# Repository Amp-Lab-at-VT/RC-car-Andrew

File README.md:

## Members
Andrew Baltus electrical engineering 2028

## Mentor
Eddie Pritchard, Ethan James

## Current Status
IN PROGRESS

## Project Overview

h

## Educational Value Added

h
## Tasks

h

## Design Decisions

## BOM + Component Cost

## Timeline

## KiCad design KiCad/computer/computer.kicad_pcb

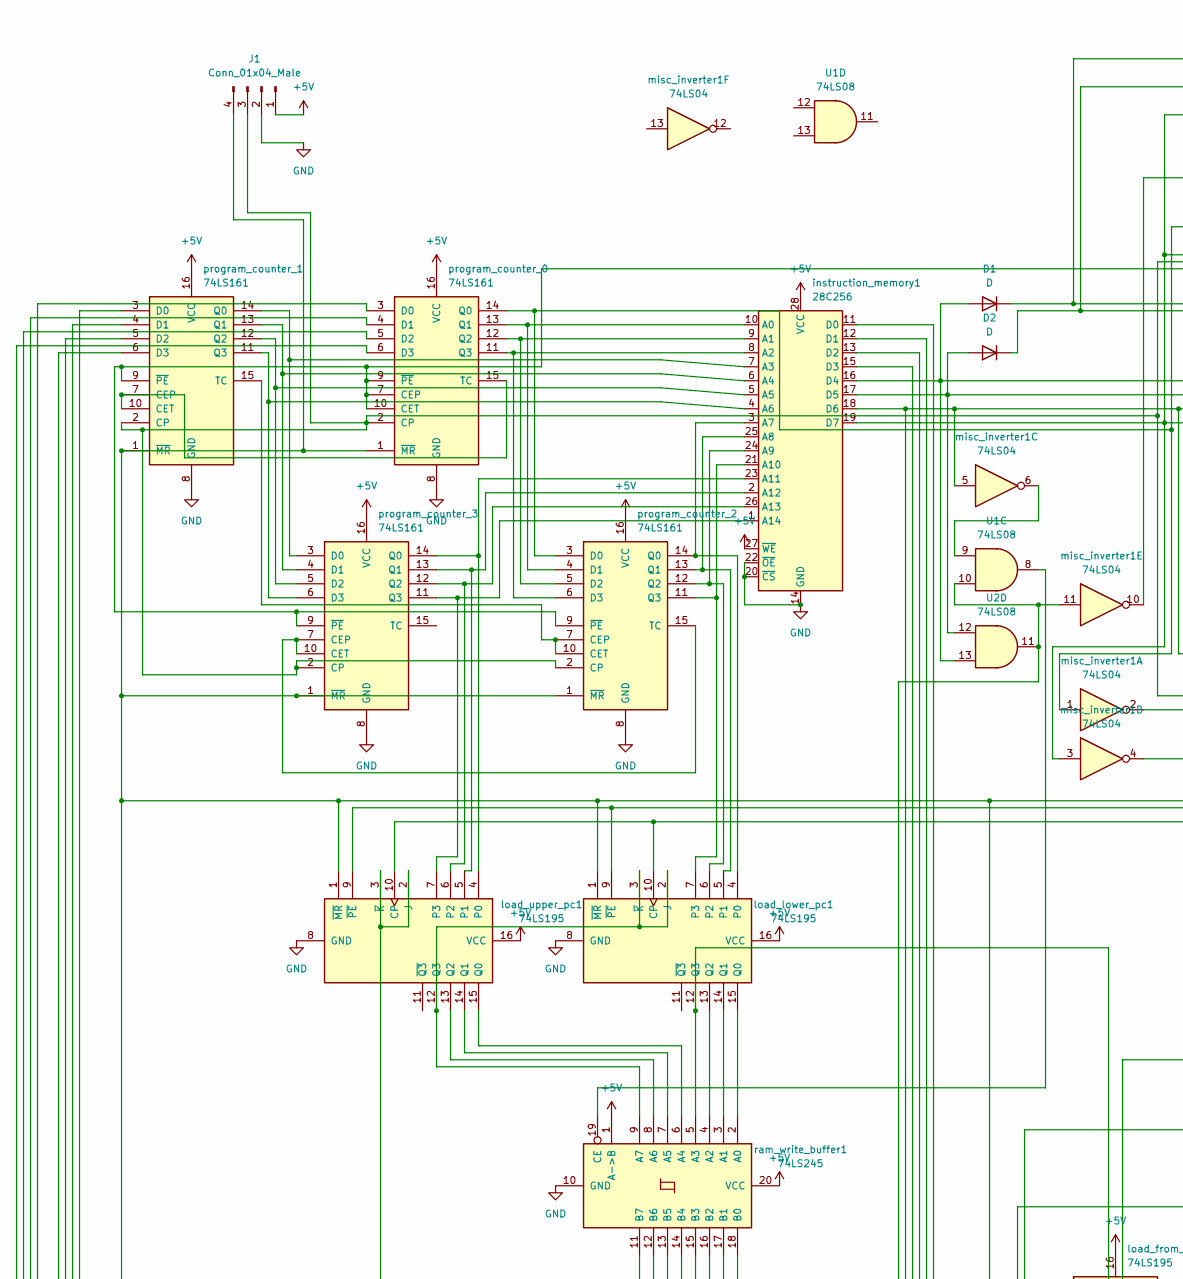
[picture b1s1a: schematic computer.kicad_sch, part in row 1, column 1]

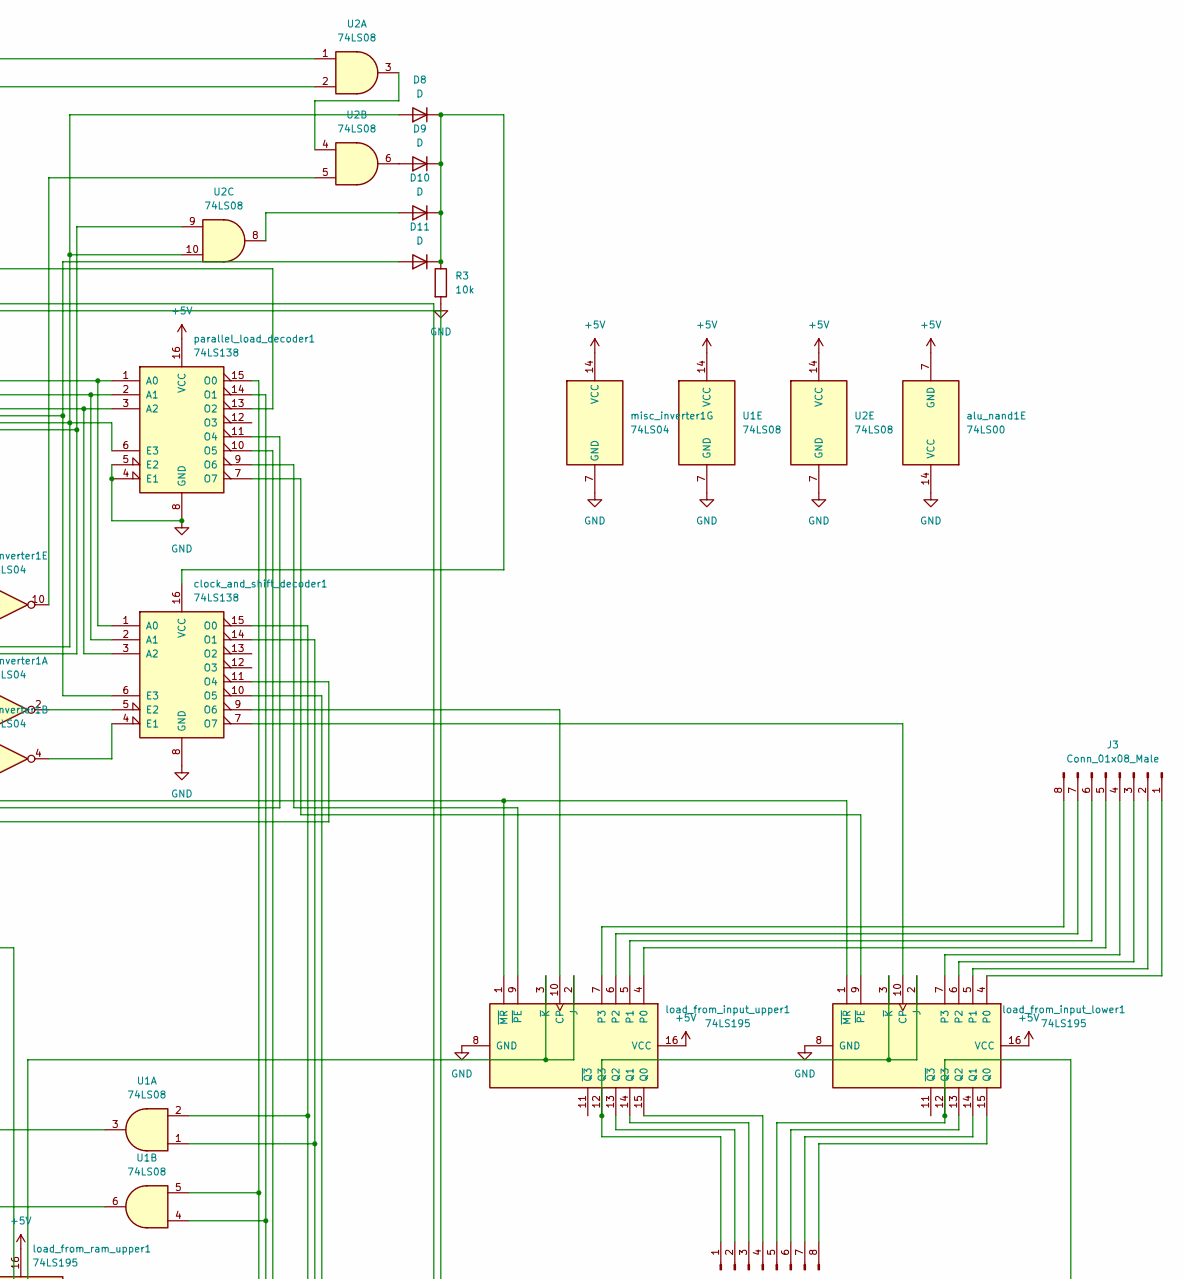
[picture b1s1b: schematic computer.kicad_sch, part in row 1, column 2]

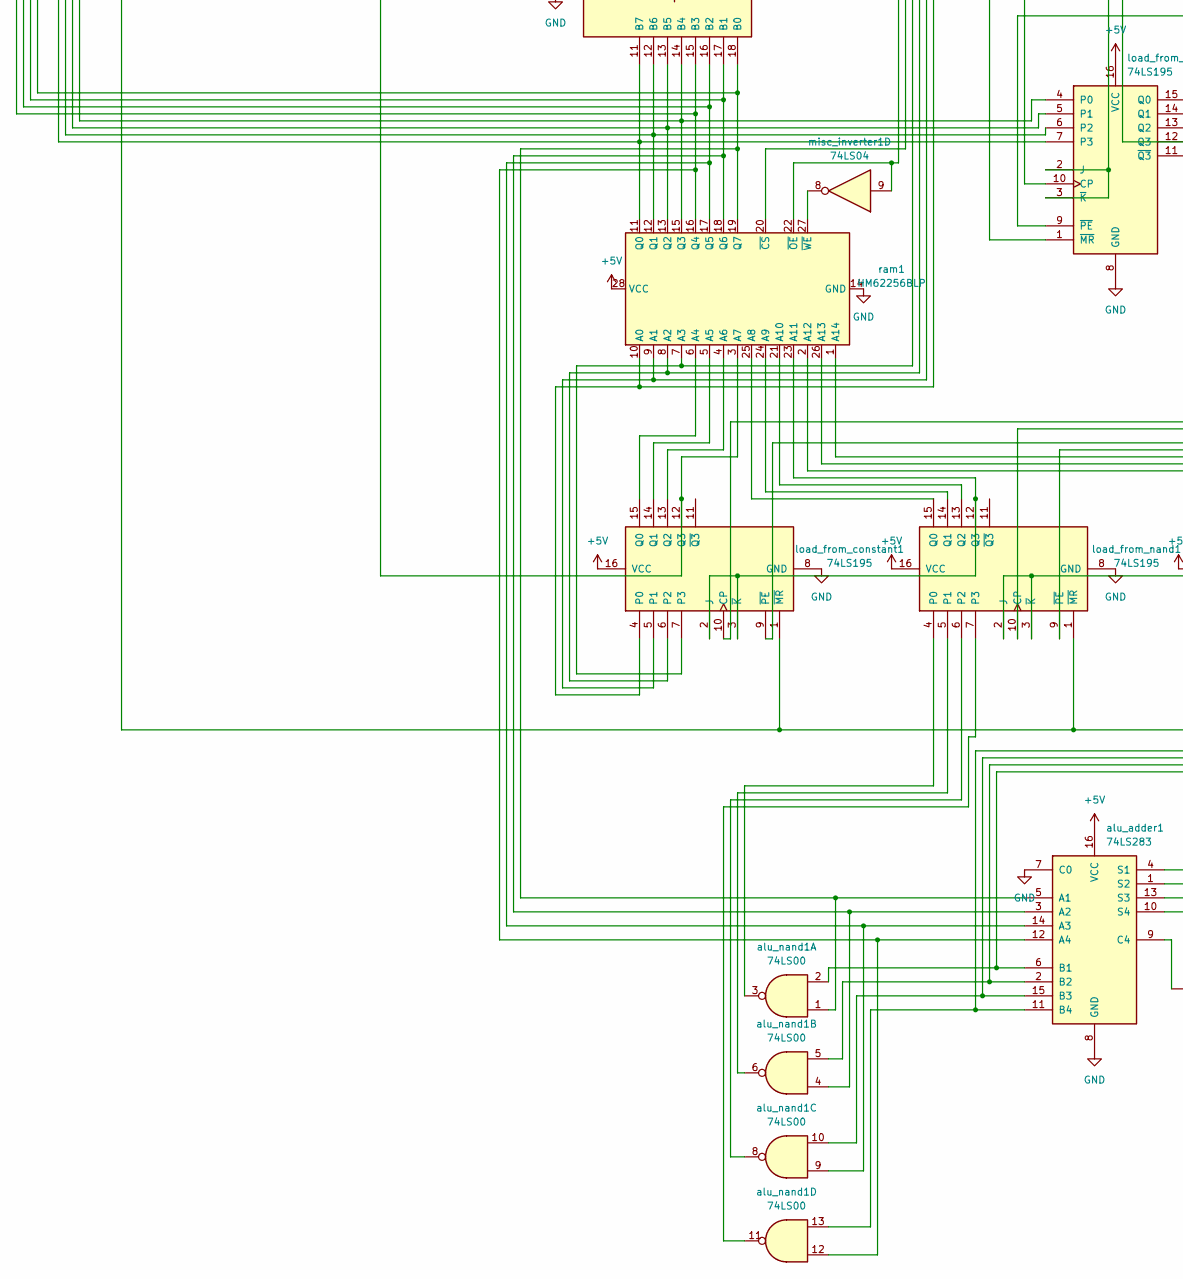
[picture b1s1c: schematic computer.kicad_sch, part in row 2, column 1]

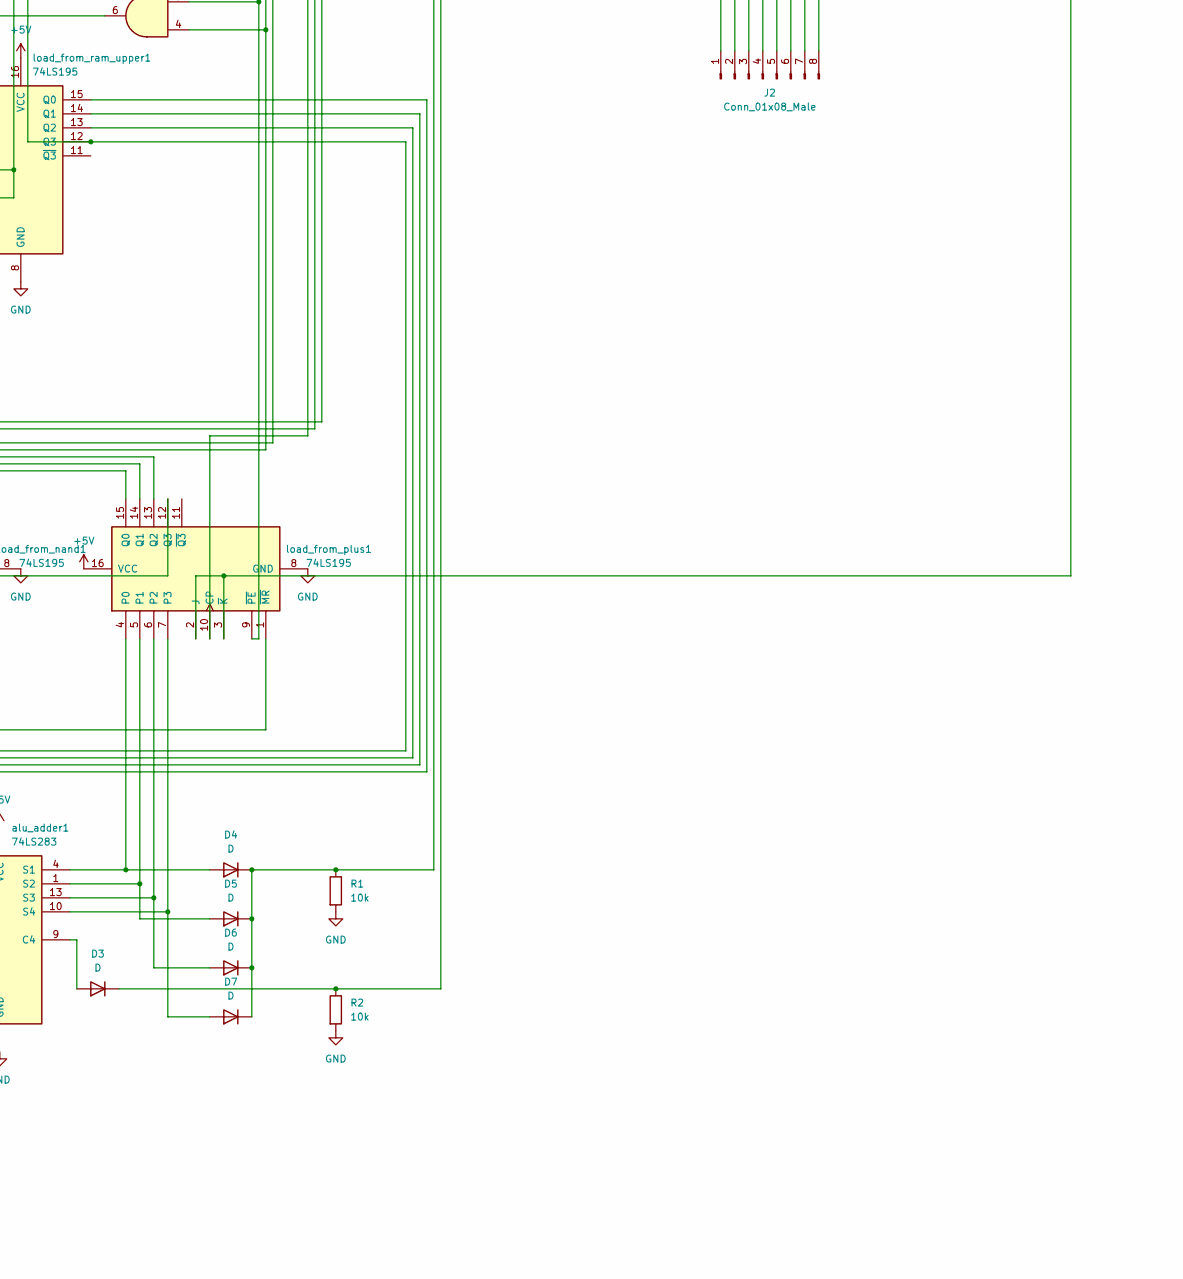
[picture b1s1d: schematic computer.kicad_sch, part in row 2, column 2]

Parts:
D1, D2, D3, D4, D5, D6, D7, D8, D9, D10, D11: D; D_DO-15_P2.54mm_Vertical_AnodeUp
J1: Conn_01x04_Male; PinHeader_1x04_P2.54mm_Vertical
J2, J3: Conn_01x08_Male; PinHeader_1x08_P2.54mm_Vertical
R1, R2, R3: 10k; R_Axial_DIN0204_L3.6mm_D1.6mm_P2.54mm_Vertical
U1, U2: 74LS08; DIP-14_W7.62mm_Socket
alu_adder1: 74LS283; DIP-16_W7.62mm_Socket
alu_nand1: 74LS00; DIP-14_W7.62mm_Socket
clock_and_shift_decoder1: 74LS138; DIP-16_W7.62mm_Socket
instruction_memory1: 28C256; DIP-28_W15.24mm_Socket
load_from_constant1: 74LS195; DIP-16_W7.62mm_Socket
load_from_input_lower1: 74LS195; DIP-16_W7.62mm_Socket
load_from_input_upper1: 74LS195; DIP-16_W7.62mm_Socket
load_from_nand1: 74LS195; DIP-16_W7.62mm_Socket
load_from_plus1: 74LS195; DIP-16_W7.62mm_Socket
load_from_ram_upper1: 74LS195; DIP-16_W7.62mm_Socket
load_lower_pc1: 74LS195; DIP-16_W7.62mm_Socket
load_upper_pc1: 74LS195; DIP-16_W7.62mm_Socket
misc_inverter1: 74LS04; DIP-14_W7.62mm_Socket
parallel_load_decoder1: 74LS138; DIP-16_W7.62mm_Socket
program_counter_0, program_counter_1, program_counter_2, program_counter_3: 74LS161; DIP-16_W7.62mm_Socket
ram1: HM62256BLP; DIP-28_W15.24mm
ram_write_buffer1: 74LS245; DIP-20_W7.62mm_Socket

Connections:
+5V: J1.1, U1.14 (VCC), U2.14 (VCC), alu_adder1.16 (VCC), alu_nand1.7 (GND), instruction_memory1.27 (~WE), instruction_memory1.28 (VCC), load_from_constant1.16 (VCC), load_from_input_lower1.16 (VCC), load_from_input_upper1.16 (VCC), load_from_nand1.16 (VCC), load_from_plus1.16 (VCC), load_from_ram_upper1.16 (VCC), load_lower_pc1.16 (VCC), load_upper_pc1.16 (VCC), misc_inverter1.14 (VCC), parallel_load_decoder1.16 (VCC), program_counter_0.16 (VCC), program_counter_1.16 (VCC), program_counter_2.16 (VCC), program_counter_3.16 (VCC), ram1.28 (VCC), ram_write_buffer1.1 (A->B), ram_write_buffer1.20 (VCC)
GND: J1.2, R1.2, R2.2, R3.2, U1.7 (GND), U2.7 (GND), alu_adder1.7 (C0), alu_adder1.8 (GND), alu_nand1.14 (VCC), clock_and_shift_decoder1.8 (GND), instruction_memory1.14 (GND), instruction_memory1.20 (~CS), instruction_memory1.22 (~OE), load_from_constant1.8 (GND), load_from_input_lower1.8 (GND), load_from_input_upper1.8 (GND), load_from_nand1.8 (GND), load_from_plus1.8 (GND), load_from_ram_upper1.8 (GND), load_lower_pc1.8 (GND), load_upper_pc1.8 (GND), misc_inverter1.7 (GND), parallel_load_decoder1.4 (E1), parallel_load_decoder1.5 (E2), parallel_load_decoder1.8 (GND), program_counter_0.8 (GND), program_counter_1.8 (GND), program_counter_2.8 (GND), program_counter_3.8 (GND), ram1.14 (GND), ram_write_buffer1.10 (GND)
unnamed: D1.1 (K), D4.1 (K), D5.1 (K), D6.1 (K), D7.1 (K), R1.1, U2.1
unnamed: D2.1 (K), D3.1 (K), R2.1, U2.2
unnamed: D9.2 (A), U2.6
unnamed: D10.2 (A), U2.8
unnamed: U2.3, U2.4
unnamed: alu_adder1.2 (B2), alu_nand1.5, load_from_ram_upper1.14 (Q1)
unnamed: alu_adder1.6 (B1), alu_nand1.2, load_from_ram_upper1.15 (Q0)
unnamed: D3.2 (A), alu_adder1.9 (C4)
unnamed: alu_adder1.11 (B4), alu_nand1.13, load_from_input_upper1.2 (J), load_from_input_upper1.3 (~K), load_from_ram_upper1.12 (Q3)
unnamed: alu_adder1.15 (B3), alu_nand1.10, load_from_ram_upper1.13 (Q2)
unnamed: clock_and_shift_decoder1.4 (E1), misc_inverter1.4
unnamed: clock_and_shift_decoder1.5 (E2), misc_inverter1.2
unnamed: D8.1 (K), D9.1 (K), D10.1 (K), D11.1 (K), R3.1, clock_and_shift_decoder1.16 (VCC)
unnamed: instruction_memory1.11 (D0), load_from_constant1.4 (P0), ram1.10 (A0)
unnamed: instruction_memory1.12 (D1), load_from_constant1.5 (P1), ram1.9 (A1)
unnamed: instruction_memory1.13 (D2), load_from_constant1.6 (P2), ram1.8 (A2)
unnamed: instruction_memory1.15 (D3), load_from_constant1.7 (P3), ram1.7 (A3)
unnamed: D1.2 (A), U2.13, clock_and_shift_decoder1.1 (A0), instruction_memory1.16 (D4), parallel_load_decoder1.1 (A0)
unnamed: D2.2 (A), U2.12, clock_and_shift_decoder1.2 (A1), instruction_memory1.17 (D5), parallel_load_decoder1.2 (A1)
unnamed: clock_and_shift_decoder1.3 (A2), instruction_memory1.18 (D6), misc_inverter1.5, parallel_load_decoder1.3 (A2), ram1.20 (~CS)
unnamed: D8.2 (A), U2.10, instruction_memory1.19 (D7), misc_inverter1.3, parallel_load_decoder1.6 (E3)
unnamed: load_from_constant1.9 (~PE), parallel_load_decoder1.10 (O5)
unnamed: clock_and_shift_decoder1.10 (O5), load_from_constant1.10 (CP)
unnamed: J3.1, load_from_input_lower1.4 (P0)
unnamed: J3.2, load_from_input_lower1.5 (P1)
unnamed: J3.3, load_from_input_lower1.6 (P2)
unnamed: J3.4, load_from_input_lower1.7 (P3)
unnamed: load_from_input_lower1.9 (~PE), parallel_load_decoder1.7 (O7)
unnamed: clock_and_shift_decoder1.7 (O7), load_from_input_lower1.10 (CP)
unnamed: J2.6, load_from_input_lower1.13 (Q2)
unnamed: J2.7, load_from_input_lower1.14 (Q1)
unnamed: J2.8, load_from_input_lower1.15 (Q0)
unnamed: J3.5, load_from_input_upper1.4 (P0)
unnamed: J3.6, load_from_input_upper1.5 (P1)
unnamed: J3.7, load_from_input_upper1.6 (P2)
unnamed: J3.8, load_from_input_upper1.7 (P3)
unnamed: load_from_input_upper1.9 (~PE), parallel_load_decoder1.9 (O6)
unnamed: clock_and_shift_decoder1.9 (O6), load_from_input_upper1.10 (CP)
unnamed: J2.1, load_from_input_lower1.2 (J), load_from_input_lower1.3 (~K), load_from_input_upper1.12 (Q3)
unnamed: J2.2, load_from_input_upper1.13 (Q2)
unnamed: J2.3, load_from_input_upper1.14 (Q1)
unnamed: J2.4, load_from_input_upper1.15 (Q0)
unnamed: load_from_nand1.2 (J), load_from_nand1.3 (~K), load_from_plus1.12 (Q3)
unnamed: alu_nand1.3, load_from_nand1.4 (P0)
unnamed: alu_nand1.6, load_from_nand1.5 (P1)
unnamed: alu_nand1.8, load_from_nand1.6 (P2)
unnamed: alu_nand1.11, load_from_nand1.7 (P3)
unnamed: U1.4, load_from_nand1.9 (~PE), parallel_load_decoder1.14 (O1)
unnamed: U1.1, clock_and_shift_decoder1.14 (O1), load_from_nand1.10 (CP)
unnamed: J2.5, load_from_input_lower1.12 (Q3), load_from_plus1.2 (J), load_from_plus1.3 (~K)
unnamed: D4.2 (A), alu_adder1.4 (S1), load_from_plus1.4 (P0)
unnamed: D5.2 (A), alu_adder1.1 (S2), load_from_plus1.5 (P1)
unnamed: D6.2 (A), alu_adder1.13 (S3), load_from_plus1.6 (P2)
unnamed: D7.2 (A), alu_adder1.10 (S4), load_from_plus1.7 (P3)
unnamed: U1.5, load_from_plus1.9 (~PE), parallel_load_decoder1.15 (O0)
unnamed: U1.2, clock_and_shift_decoder1.15 (O0), load_from_plus1.10 (CP)
unnamed: U1.6, load_from_ram_upper1.9 (~PE)
unnamed: U1.3, load_from_ram_upper1.10 (CP)
unnamed: load_from_ram_upper1.2 (J), load_from_ram_upper1.3 (~K), load_lower_pc1.12 (Q3), ram_write_buffer1.5 (A3)
unnamed: load_lower_pc1.13 (Q2), ram_write_buffer1.4 (A2)
unnamed: load_lower_pc1.14 (Q1), ram_write_buffer1.3 (A1)
unnamed: load_lower_pc1.15 (Q0), ram_write_buffer1.2 (A0)
unnamed: load_from_constant1.12 (Q3), load_upper_pc1.2 (J), load_upper_pc1.3 (~K), ram1.3 (A7)
unnamed: load_lower_pc1.9 (~PE), load_upper_pc1.9 (~PE), parallel_load_decoder1.11 (O4)
unnamed: clock_and_shift_decoder1.11 (O4), load_lower_pc1.10 (CP), load_upper_pc1.10 (CP)
unnamed: load_lower_pc1.2 (J), load_lower_pc1.3 (~K), load_upper_pc1.12 (Q3), ram_write_buffer1.9 (A7)
unnamed: load_upper_pc1.13 (Q2), ram_write_buffer1.8 (A6)
unnamed: load_upper_pc1.14 (Q1), ram_write_buffer1.7 (A5)
unnamed: load_upper_pc1.15 (Q0), ram_write_buffer1.6 (A4)
unnamed: U1.9, misc_inverter1.6
unnamed: U2.5, misc_inverter1.10
unnamed: alu_adder1.5 (A1), alu_nand1.1, program_counter_0.3 (D0), ram1.19 (Q7), ram_write_buffer1.18 (B0)
unnamed: alu_adder1.3 (A2), alu_nand1.4, program_counter_0.4 (D1), ram1.18 (Q6), ram_write_buffer1.17 (B1)
unnamed: alu_adder1.14 (A3), alu_nand1.9, program_counter_0.5 (D2), ram1.17 (Q5), ram_write_buffer1.16 (B2)
unnamed: alu_adder1.12 (A4), alu_nand1.12, program_counter_0.6 (D3), ram1.16 (Q4), ram_write_buffer1.15 (B3)
unnamed: instruction_memory1.8 (A2), program_counter_0.11 (Q3), program_counter_2.6 (D3)
unnamed: instruction_memory1.9 (A1), program_counter_0.12 (Q2), program_counter_2.5 (D2)
unnamed: instruction_memory1.10 (A0), program_counter_0.13 (Q1), program_counter_2.4 (D1)
unnamed: U2.9, misc_inverter1.1, program_counter_0.14 (Q0), program_counter_2.3 (D0)
unnamed: J1.4, load_from_constant1.1 (~MR), load_from_input_lower1.1 (~MR), load_from_input_upper1.1 (~MR), load_from_nand1.1 (~MR), load_from_plus1.1 (~MR), load_from_ram_upper1.1 (~MR), load_lower_pc1.1 (~MR), load_upper_pc1.1 (~MR), program_counter_0.1 (~MR), program_counter_1.1 (~MR), program_counter_2.1 (~MR), program_counter_3.1 (~MR)
unnamed: D11.2 (A), J1.3, clock_and_shift_decoder1.6 (E3), program_counter_0.2 (CP), program_counter_1.2 (CP), program_counter_2.2 (CP), program_counter_3.2 (CP)
unnamed: load_from_ram_upper1.4 (P0), program_counter_1.3 (D0), ram1.15 (Q3), ram_write_buffer1.14 (B4)
unnamed: load_from_ram_upper1.5 (P1), program_counter_1.4 (D1), ram1.13 (Q2), ram_write_buffer1.13 (B5)
unnamed: load_from_ram_upper1.6 (P2), program_counter_1.5 (D2), ram1.12 (Q1), ram_write_buffer1.12 (B6)
unnamed: load_from_ram_upper1.7 (P3), program_counter_1.6 (D3), ram1.11 (Q0), ram_write_buffer1.11 (B7)
unnamed: parallel_load_decoder1.13 (O2), program_counter_0.7 (CEP), program_counter_0.9 (~PE), program_counter_0.10 (CET), program_counter_1.9 (~PE), program_counter_2.9 (~PE), program_counter_3.9 (~PE)
unnamed: program_counter_0.15 (TC), program_counter_1.7 (CEP), program_counter_1.10 (CET)
unnamed: instruction_memory1.4 (A6), program_counter_1.11 (Q3), program_counter_3.6 (D3)
unnamed: instruction_memory1.5 (A5), program_counter_1.12 (Q2), program_counter_3.5 (D2)
unnamed: instruction_memory1.6 (A4), program_counter_1.13 (Q1), program_counter_3.4 (D1)
unnamed: instruction_memory1.7 (A3), program_counter_1.14 (Q0), program_counter_3.3 (D0)
unnamed: program_counter_1.15 (TC), program_counter_2.7 (CEP), program_counter_2.10 (CET)
unnamed: instruction_memory1.21 (A10), load_lower_pc1.7 (P3), program_counter_2.11 (Q3)
unnamed: instruction_memory1.24 (A9), load_lower_pc1.6 (P2), program_counter_2.12 (Q2)
unnamed: instruction_memory1.25 (A8), load_lower_pc1.5 (P1), program_counter_2.13 (Q1)
unnamed: instruction_memory1.3 (A7), load_lower_pc1.4 (P0), program_counter_2.14 (Q0)
unnamed: program_counter_2.15 (TC), program_counter_3.7 (CEP), program_counter_3.10 (CET)
unnamed: instruction_memory1.1 (A14), load_upper_pc1.7 (P3), program_counter_3.11 (Q3)
unnamed: instruction_memory1.26 (A13), load_upper_pc1.6 (P2), program_counter_3.12 (Q2)
unnamed: instruction_memory1.2 (A12), load_upper_pc1.5 (P1), program_counter_3.13 (Q1)
unnamed: instruction_memory1.23 (A11), load_upper_pc1.4 (P0), program_counter_3.14 (Q0)
unnamed: load_from_plus1.13 (Q2), ram1.1 (A14)
unnamed: load_from_plus1.15 (Q0), ram1.2 (A12)
unnamed: load_from_constant1.13 (Q2), ram1.4 (A6)
unnamed: load_from_constant1.14 (Q1), ram1.5 (A5)
unnamed: load_from_constant1.15 (Q0), ram1.6 (A4)
unnamed: load_from_nand1.13 (Q2), ram1.21 (A10)
unnamed: U1.10, U2.11, misc_inverter1.9, misc_inverter1.11, ram1.22 (~OE)
unnamed: load_from_constant1.2 (J), load_from_constant1.3 (~K), load_from_nand1.12 (Q3), ram1.23 (A11)
unnamed: load_from_nand1.14 (Q1), ram1.24 (A9)
unnamed: load_from_nand1.15 (Q0), ram1.25 (A8)
unnamed: load_from_plus1.14 (Q1), ram1.26 (A13)
unnamed: misc_inverter1.8, ram1.27 (~WE)
unnamed: U1.8, ram_write_buffer1.19 (CE)

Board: 2 copper layers, 39 parts (0 on the bottom side), 116 nets, no tracks yet.

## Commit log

2024-02-01 Create p2.txt
    Writing basic write/ream programs for ram
2024-02-14 reorg
2024-02-20 assembler version two
2024-02-20 oh this is kinda cool
2024-02-20 working simulator jumps
2024-02-21 push
2024-02-21 pushy
